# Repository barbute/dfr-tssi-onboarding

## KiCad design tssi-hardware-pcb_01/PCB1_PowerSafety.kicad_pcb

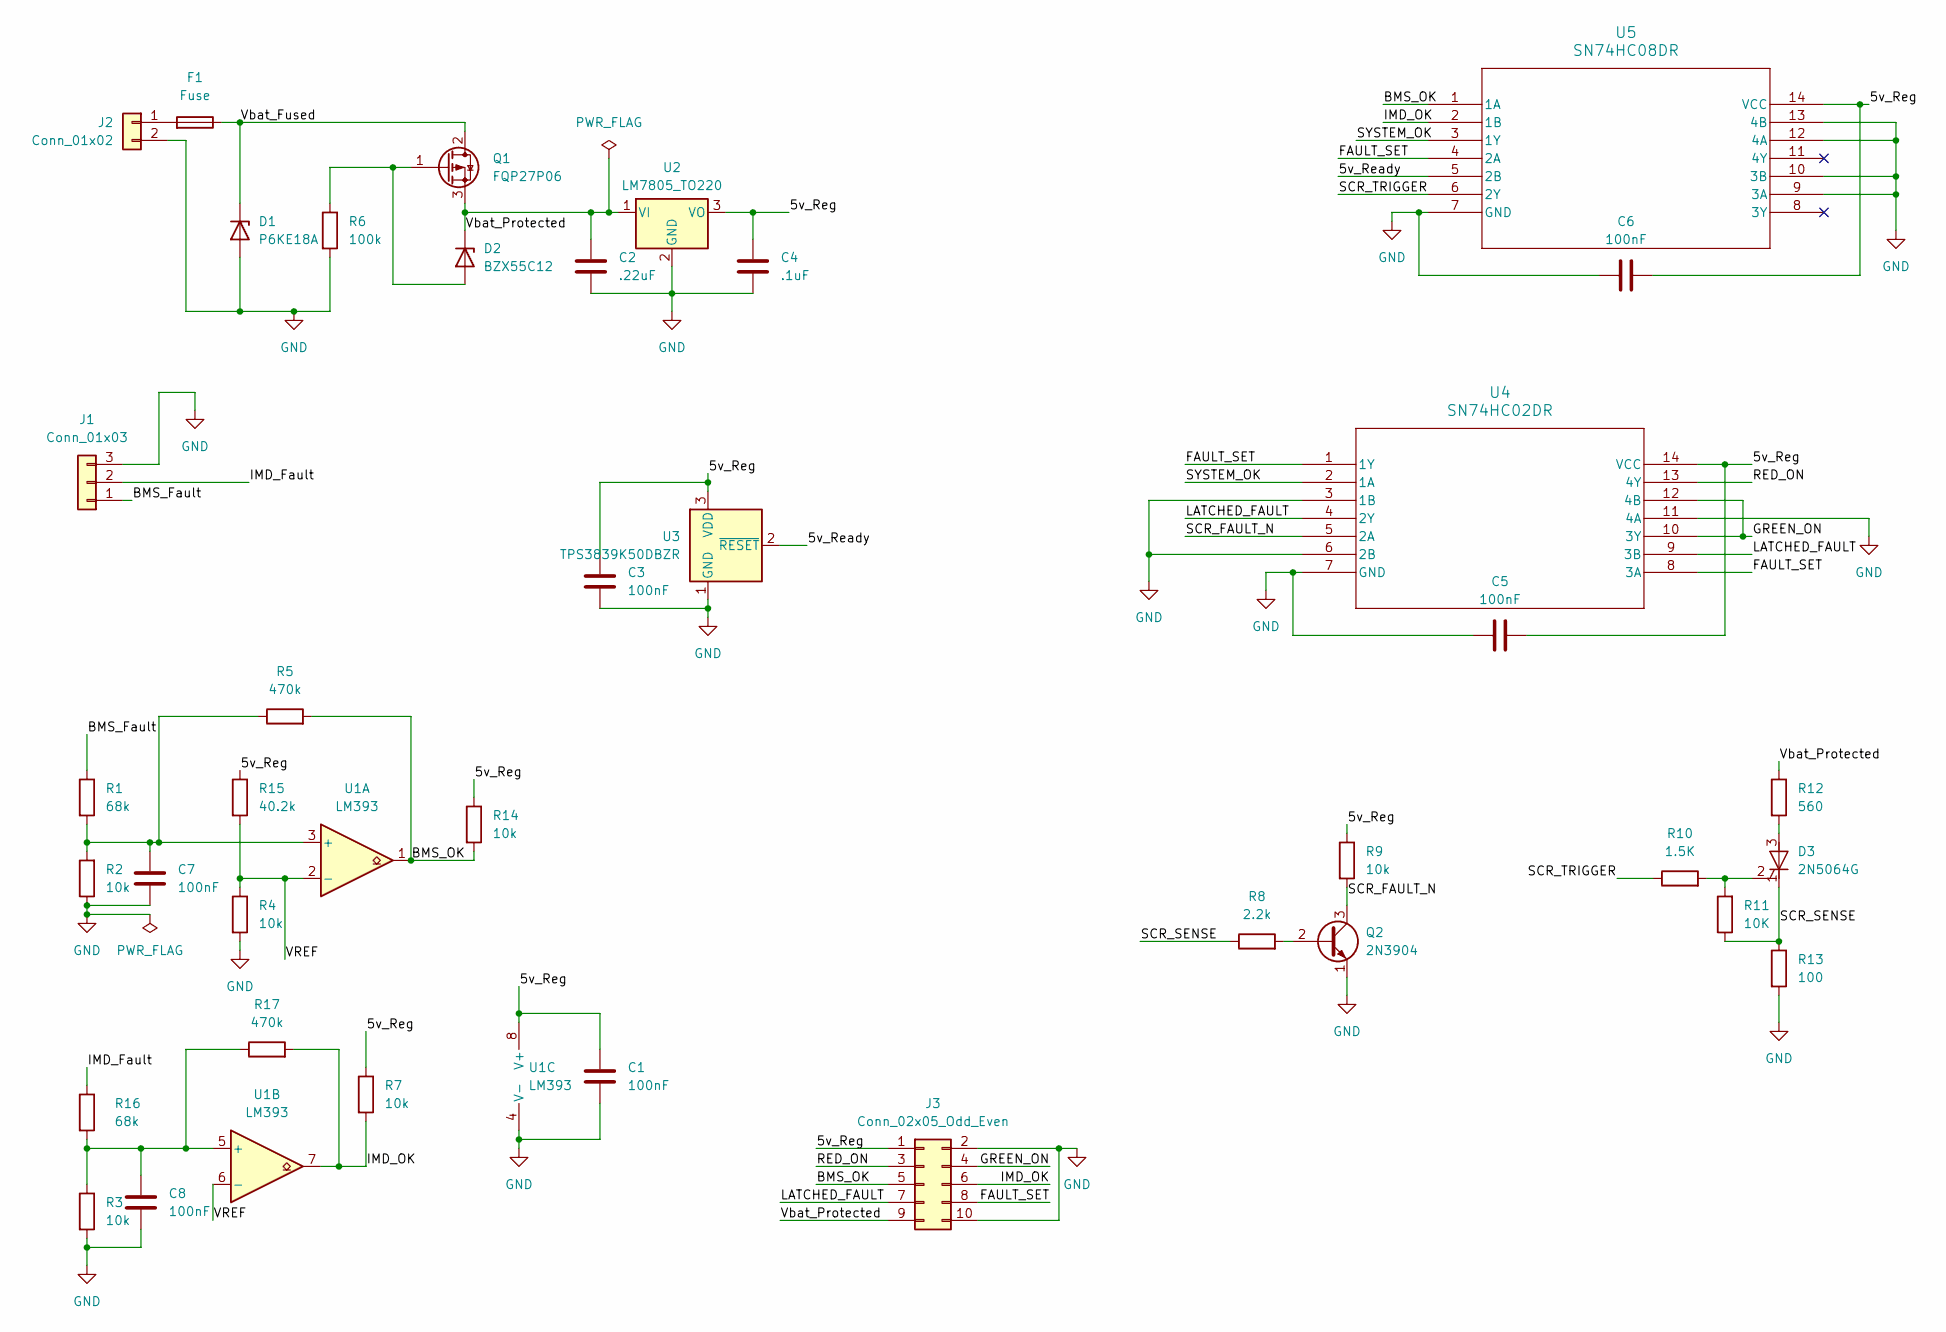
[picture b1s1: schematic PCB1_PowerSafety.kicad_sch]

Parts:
C1, C3, C5, C6: 100nF; C_0805_2012Metric
C2: .22uF; C_0805_2012Metric
C4: .1uF; C_0805_2012Metric
C7, C8: 100nF; C_Disc_D5.0mm_W2.5mm_P5.00mm
D1: P6KE18A; D_DO-15_P10.16mm_Horizontal
D2: BZX55C12; D_DO-15_P10.16mm_Horizontal
D3: 2N5064G; TO-92_Inline
F1: Fuse; Fuseholder_Blade_Mini_Keystone_3568
J1: Conn_01x03; PinHeader_1x03_P2.54mm_Vertical
J2: Conn_01x02; PinHeader_1x02_P2.54mm_Vertical
J3: Conn_02x05_Odd_Even; PinHeader_2x05_P2.54mm_Vertical
Q1: FQP27P06; TO-220-3_Vertical
Q2: 2N3904; TO-92_Inline
R1, R16: 68k; R_Axial_DIN0207_L6.3mm_D2.5mm_P7.62mm_Horizontal
R2, R3, R4, R7, R9, R14: 10k; R_Axial_DIN0207_L6.3mm_D2.5mm_P7.62mm_Horizontal
R5, R17: 470k; R_Axial_DIN0207_L6.3mm_D2.5mm_P7.62mm_Horizontal
R6: 100k; R_Axial_DIN0207_L6.3mm_D2.5mm_P7.62mm_Horizontal
R8: 2.2k; R_Axial_DIN0207_L6.3mm_D2.5mm_P7.62mm_Horizontal
R10: 1.5K; R_Axial_DIN0207_L6.3mm_D2.5mm_P7.62mm_Horizontal
R11: 10K; R_Axial_DIN0207_L6.3mm_D2.5mm_P7.62mm_Horizontal
R12: 560; R_Axial_DIN0309_L9.0mm_D3.2mm_P12.70mm_Horizontal
R13: 100; R_Axial_DIN0207_L6.3mm_D2.5mm_P7.62mm_Horizontal
R15: 40.2k; R_Axial_DIN0207_L6.3mm_D2.5mm_P7.62mm_Horizontal
U1: LM393; SOIC-8_3.9x4.9mm_P1.27mm
U2: LM7805_TO220; TO-220-3_Vertical
U3: TPS3839K50DBZR; SOT-23
U4: SN74HC02DR; D14
U5: SN74HC08DR; D14

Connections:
/5v_Ready: U3.2 (~RESET), U5.5 (2B)
/5v_Reg: C1.1, C3.1, C4.1, C5.2, C6.2, J3.1, R7.1, R9.1, R14.1, R15.1, U1.8 (V+), U2.3 (VO), U3.3 (VDD), U4.14 (VCC), U5.14 (VCC)
/BMS_Fault: J1.1, R1.1
/BMS_OK: J3.5, R5.2, R14.2, U1.1, U5.1 (1A)
/FAULT_SET: J3.8, U4.1 (1Y), U4.8 (3A), U5.4 (2A)
/GREEN_ON: J3.4, U4.10 (3Y), U4.12 (4B)
/IMD_Fault: J1.2, R16.1
/IMD_OK: J3.6, R7.2, R17.2, U1.7, U5.2 (1B)
/LATCHED_FAULT: J3.7, U4.4 (2Y), U4.9 (3B)
/RED_ON: J3.3, U4.13 (4Y)
/SCR_FAULT_N: Q2.3 (C), R9.2, U4.5 (2A)
/SCR_SENSE: D3.1 (K), R8.1, R11.1, R13.1
/SCR_TRIGGER: R10.1, U5.6 (2Y)
/SYSTEM_OK: U4.2 (1A), U5.3 (1Y)
/VREF: R4.1, R15.2, U1.2 (-), U1.6 (-)
/Vbat_Fused: D1.1 (K), F1.1, Q1.2 (D)
/Vbat_Protected: C2.1, D2.1 (K), J3.9, Q1.3 (S), R12.1, U2.1 (VI)
GND: C1.2, C2.2, C3.2, C4.2, C5.1, C6.1, C7.2, C8.2, D1.2 (A), J1.3, J2.2, J3.2, J3.10, Q2.1 (E), R2.1, R3.2, R4.2, R6.2, R13.2, U1.4 (V-), U2.2 (GND), U3.1 (GND), U4.3 (1B), U4.6 (2B), U4.7 (GND), U4.11 (4A), U5.7 (GND), U5.9 (3A), U5.10 (3B), U5.12 (4A), U5.13 (4B)
unnamed: D2.2 (A), Q1.1 (G), R6.1
unnamed: D3.3 (A), R12.2
unnamed: D3.2 (G), R10.2, R11.2
unnamed: F1.2, J2.1
unnamed: Q2.2 (B), R8.2
unnamed: C7.1, R1.2, R2.2, R5.1, U1.3 (+)
unnamed: C8.1, R3.1, R16.2, R17.1, U1.5 (+)

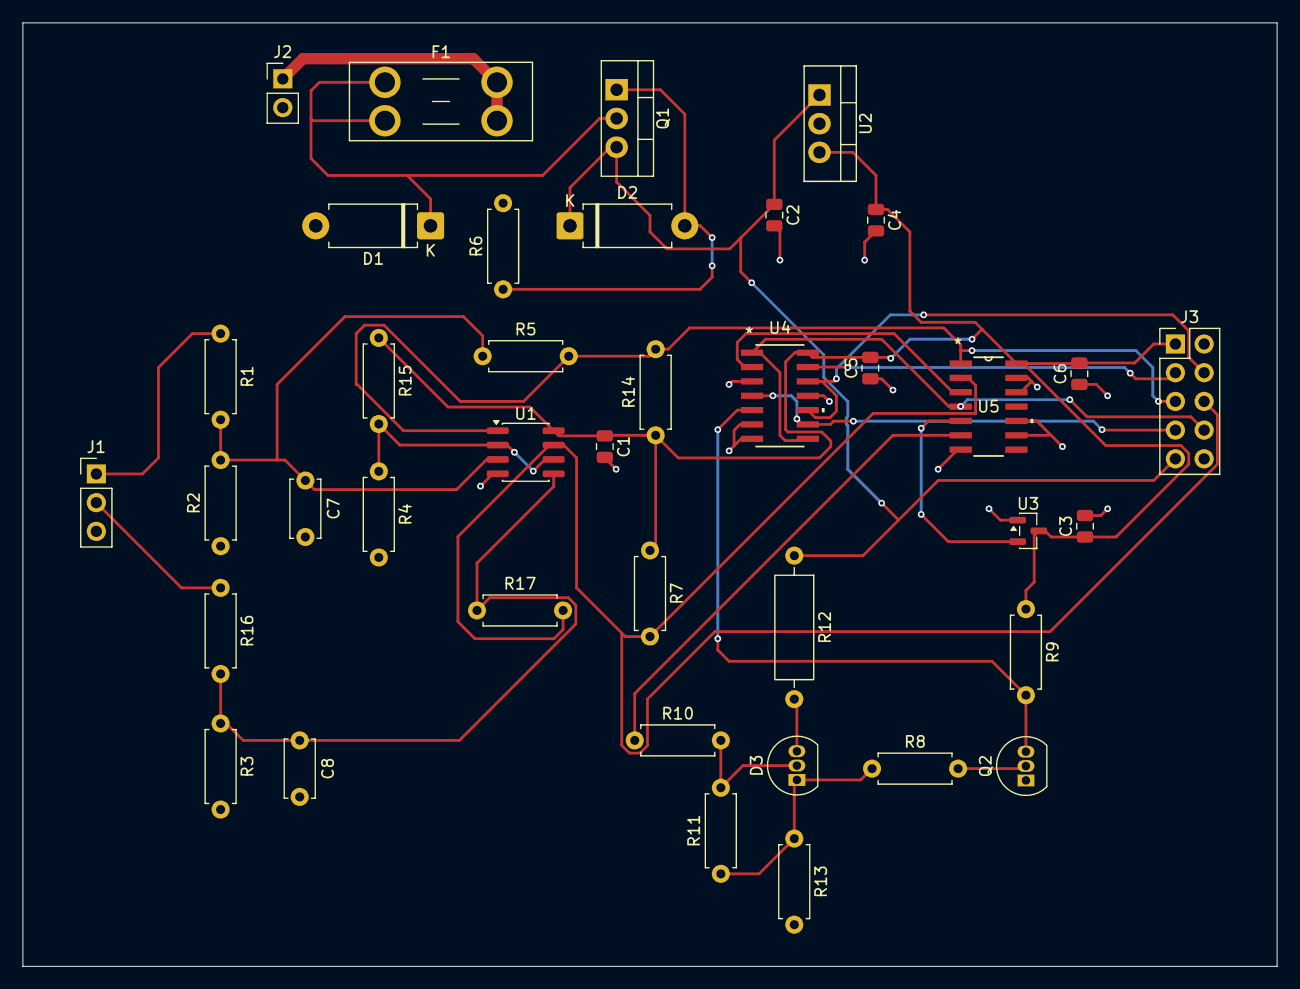
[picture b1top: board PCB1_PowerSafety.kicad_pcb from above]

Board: 2 copper layers, 111.0 x 83.5 mm, 39 parts (0 on the bottom side), 25 nets.
